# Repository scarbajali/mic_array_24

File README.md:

# mic_array_24
PCB of a 24-MEMS microphones array

**Software:** Kicad

**3D Preview:**

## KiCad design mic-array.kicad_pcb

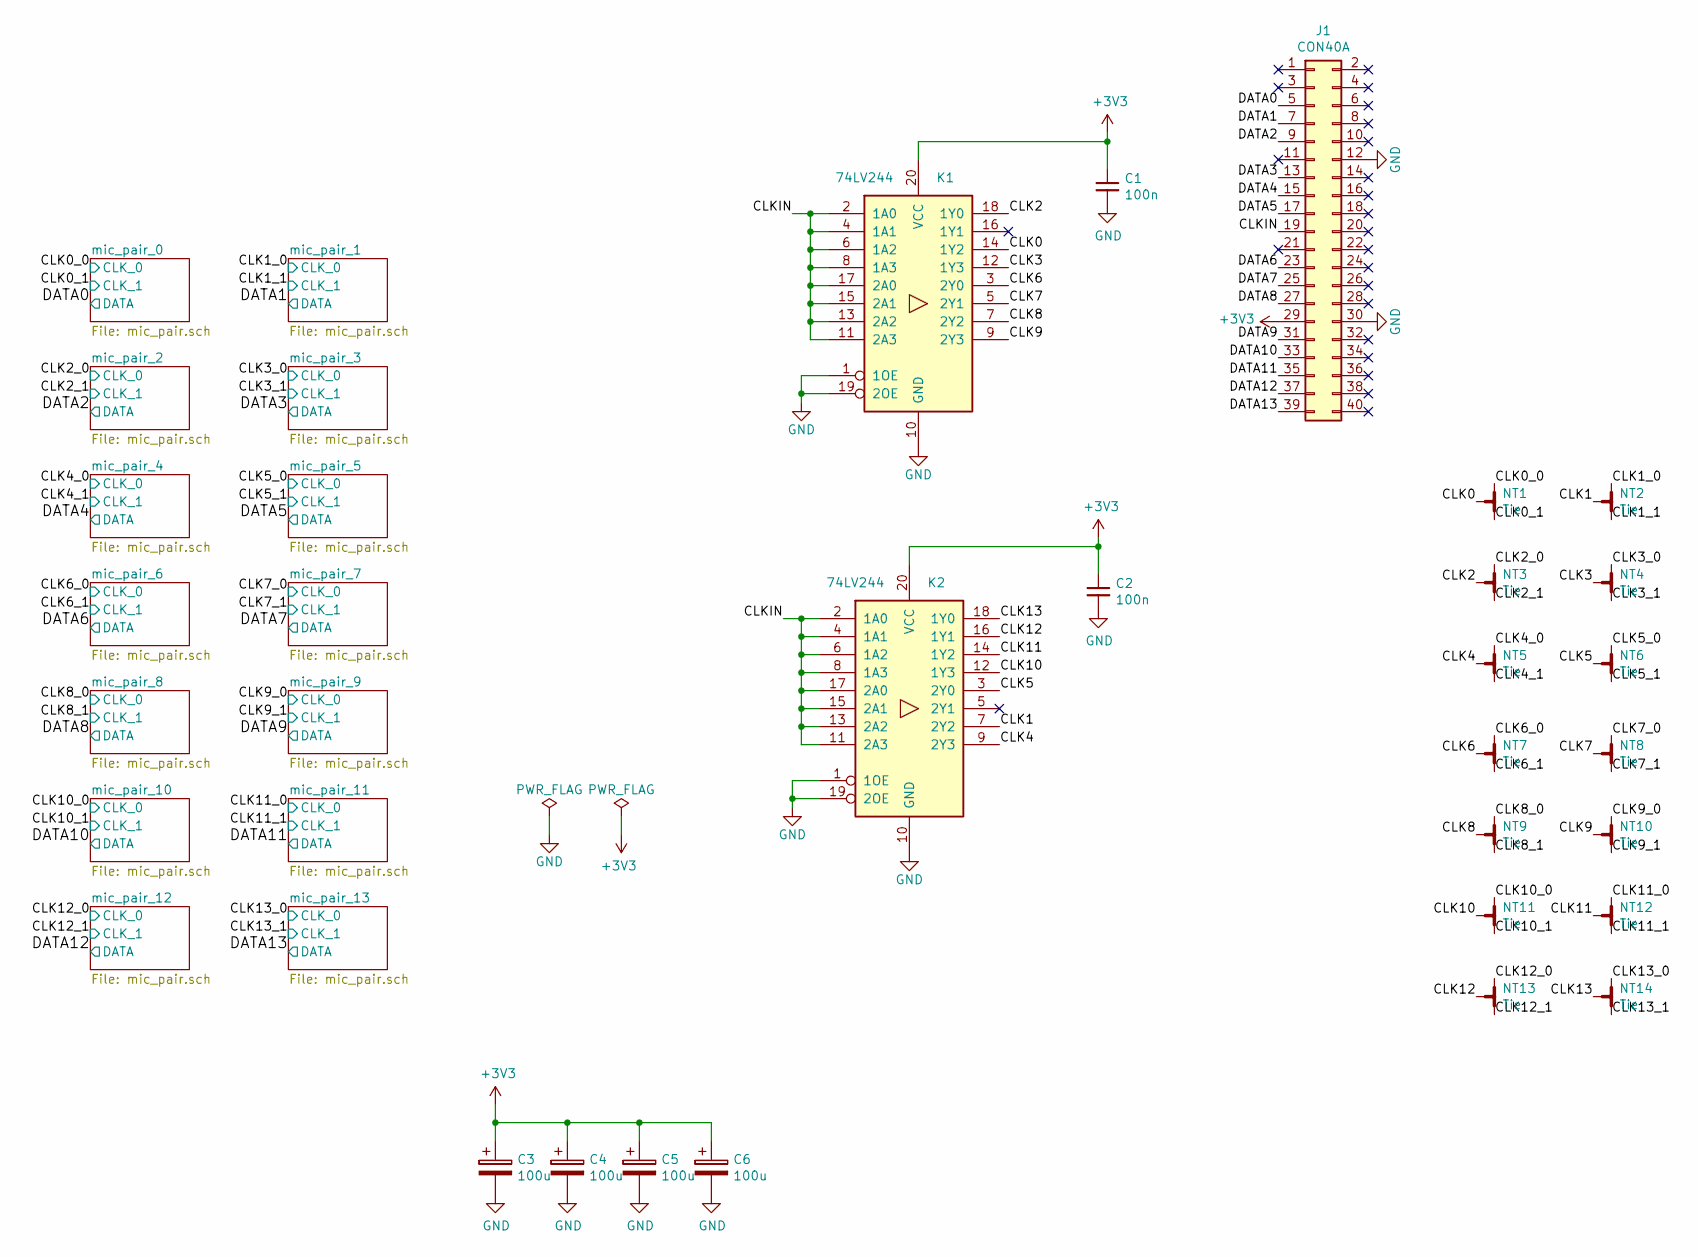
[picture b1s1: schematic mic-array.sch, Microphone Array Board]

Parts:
C1, C2: 100n; C_0603_1608Metric_Pad1.05x0.95mm_HandSolder
C3, C4, C5, C6: 100u; CP_Elec_3x5.3
J1: CON40A; PinSocket_2x20_P2.54mm_Vertical
K1, K2: 74LV244; SSOP-20_4.4x6.5mm_P0.65mm
NT1, NT2, NT3, NT4, NT5, NT6, NT7, NT8, NT9, NT10, NT11, NT12, NT13, NT14: Tie; bridge_1x2_0.12mm

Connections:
+3V3: C1.1, C2.1, C3.1, C4.1, C5.1, C6.1, J1.29, K1.20 (VCC), K2.20 (VCC); also elsewhere on the board
/CLK0: K1.14 (1Y2), NT1.3
/CLK0_0: NT1.1; also elsewhere on the board
/CLK0_1: NT1.2; also elsewhere on the board
/CLK1: K2.7 (2Y2), NT2.3
/CLK1_0: NT2.1; also elsewhere on the board
/CLK1_1: NT2.2; also elsewhere on the board
/CLK2: K1.18 (1Y0), NT3.3
/CLK2_0: NT3.1; also elsewhere on the board
/CLK2_1: NT3.2; also elsewhere on the board
/CLK3: K1.12 (1Y3), NT4.3
/CLK3_0: NT4.1; also elsewhere on the board
/CLK3_1: NT4.2; also elsewhere on the board
/CLK4: K2.9 (2Y3), NT5.3
/CLK4_0: NT5.1; also elsewhere on the board
/CLK4_1: NT5.2; also elsewhere on the board
/CLK5: K2.3 (2Y0), NT6.3
/CLK5_0: NT6.1; also elsewhere on the board
/CLK5_1: NT6.2; also elsewhere on the board
/CLK6: K1.3 (2Y0), NT7.3
/CLK6_0: NT7.1; also elsewhere on the board
/CLK6_1: NT7.2; also elsewhere on the board
/CLK7: K1.5 (2Y1), NT8.3
/CLK7_0: NT8.1; also elsewhere on the board
/CLK7_1: NT8.2; also elsewhere on the board
/CLK8: K1.7 (2Y2), NT9.3
/CLK8_0: NT9.1; also elsewhere on the board
/CLK8_1: NT9.2; also elsewhere on the board
/CLK9: K1.9 (2Y3), NT10.3
/CLK9_0: NT10.1; also elsewhere on the board
/CLK9_1: NT10.2; also elsewhere on the board
/CLK10: K2.12 (1Y3), NT11.3
/CLK10_0: NT11.1; also elsewhere on the board
/CLK10_1: NT11.2; also elsewhere on the board
/CLK11: K2.14 (1Y2), NT12.3
/CLK11_0: NT12.1; also elsewhere on the board
/CLK11_1: NT12.2; also elsewhere on the board
/CLK12: K2.16 (1Y1), NT13.3
/CLK12_0: NT13.1; also elsewhere on the board
/CLK12_1: NT13.2; also elsewhere on the board
/CLK13: K2.18 (1Y0), NT14.3
/CLK13_0: NT14.1; also elsewhere on the board
/CLK13_1: NT14.2; also elsewhere on the board
/CLKIN: J1.19, K1.2 (1A0), K1.4 (1A1), K1.6 (1A2), K1.8 (1A3), K1.11 (2A3), K1.13 (2A2), K1.15 (2A1), K1.17 (2A0), K2.2 (1A0), K2.4 (1A1), K2.6 (1A2), K2.8 (1A3), K2.11 (2A3), K2.13 (2A2), K2.15 (2A1), K2.17 (2A0)
/DATA0: J1.5; also elsewhere on the board
/DATA1: J1.7; also elsewhere on the board
/DATA2: J1.9; also elsewhere on the board
/DATA3: J1.13; also elsewhere on the board
/DATA4: J1.15; also elsewhere on the board
/DATA5: J1.17; also elsewhere on the board
/DATA6: J1.23; also elsewhere on the board
/DATA7: J1.25; also elsewhere on the board
/DATA8: J1.27; also elsewhere on the board
/DATA9: J1.31; also elsewhere on the board
/DATA10: J1.33; also elsewhere on the board
/DATA11: J1.35; also elsewhere on the board
/DATA12: J1.37; also elsewhere on the board
/DATA13: J1.39; also elsewhere on the board
GND: C1.2, C2.2, C3.2, C4.2, C5.2, C6.2, J1.12, J1.30, K1.1 (1OE), K1.10 (GND), K1.19 (2OE), K2.1 (1OE), K2.10 (GND), K2.19 (2OE); also elsewhere on the board

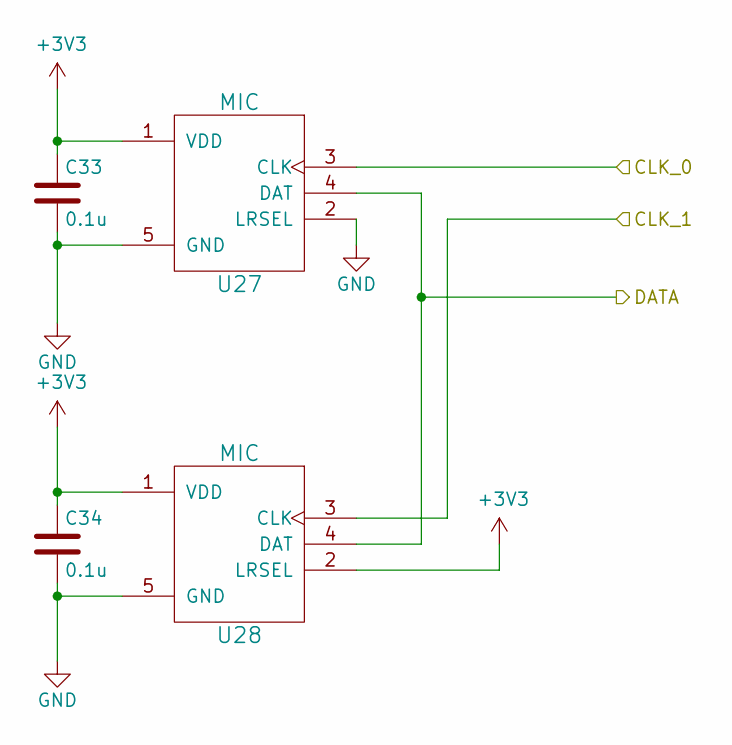
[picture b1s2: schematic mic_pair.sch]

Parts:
C7, C8: 0.1u; C_0603_1608Metric_Pad1.05x0.95mm_HandSolder
U1, U2: MIC; MIC_WM7216

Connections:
+3V3: C7.1, C8.1, U1.1 (VDD), U2.1 (VDD), U2.2 (LRSEL); also elsewhere on the board
/CLK0_0: U1.3 (CLK); also elsewhere on the board
/CLK0_1: U2.3 (CLK); also elsewhere on the board
/DATA0: U1.4 (DAT), U2.4 (DAT); also elsewhere on the board
GND: C7.2, C8.2, U1.2 (LRSEL), U1.5 (GND), U2.5 (GND); also elsewhere on the board

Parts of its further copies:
C9, C10, C11, C12, C13, C14, C15, C16, C17, C18, C19, C20, C21, C22, C23, C24, C25, C26, C27, C28, C29, C30, C31, C32, C33, C34: 0.1u; C_0603_1608Metric_Pad1.05x0.95mm_HandSolder
U3, U4, U5, U6, U7, U8, U9, U10, U11, U12, U13, U14, U15, U16, U17, U18, U19, U20, U21, U22, U23, U24, U25, U26, U27, U28: MIC; MIC_WM7216

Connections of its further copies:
+3V3: C9.1, C10.1, C11.1, C12.1, C13.1, C14.1, C15.1, C16.1, C17.1, C18.1, C19.1, C20.1, C21.1, C22.1, C23.1, C24.1, C25.1, C26.1, C27.1, C28.1, C29.1, C30.1, C31.1, C32.1, C33.1, C34.1, U3.1 (VDD), U4.1 (VDD), U4.2 (LRSEL), U5.1 (VDD), U6.1 (VDD), U6.2 (LRSEL), U7.1 (VDD), U8.1 (VDD), U8.2 (LRSEL), U9.1 (VDD), U10.1 (VDD), U10.2 (LRSEL), U11.1 (VDD), U12.1 (VDD), U12.2 (LRSEL), U13.1 (VDD), U14.1 (VDD), U14.2 (LRSEL), U15.1 (VDD), U16.1 (VDD), U16.2 (LRSEL), U17.1 (VDD), U18.1 (VDD), U18.2 (LRSEL), U19.1 (VDD), U20.1 (VDD), U20.2 (LRSEL), U21.1 (VDD), U22.1 (VDD), U22.2 (LRSEL), U23.1 (VDD), U24.1 (VDD), U24.2 (LRSEL), U25.1 (VDD), U26.1 (VDD), U26.2 (LRSEL), U27.1 (VDD), U28.1 (VDD), U28.2 (LRSEL); also elsewhere on the board
/CLK1_0: U3.3 (CLK); also elsewhere on the board
/CLK1_1: U4.3 (CLK); also elsewhere on the board
/CLK2_0: U5.3 (CLK); also elsewhere on the board
/CLK2_1: U6.3 (CLK); also elsewhere on the board
/CLK3_0: U7.3 (CLK); also elsewhere on the board
/CLK3_1: U8.3 (CLK); also elsewhere on the board
/CLK4_0: U9.3 (CLK); also elsewhere on the board
/CLK4_1: U10.3 (CLK); also elsewhere on the board
/CLK5_0: U11.3 (CLK); also elsewhere on the board
/CLK5_1: U12.3 (CLK); also elsewhere on the board
/CLK6_0: U13.3 (CLK); also elsewhere on the board
/CLK6_1: U14.3 (CLK); also elsewhere on the board
/CLK7_0: U15.3 (CLK); also elsewhere on the board
/CLK7_1: U16.3 (CLK); also elsewhere on the board
/CLK8_0: U17.3 (CLK); also elsewhere on the board
/CLK8_1: U18.3 (CLK); also elsewhere on the board
/CLK9_0: U19.3 (CLK); also elsewhere on the board
/CLK9_1: U20.3 (CLK); also elsewhere on the board
/CLK10_0: U21.3 (CLK); also elsewhere on the board
/CLK10_1: U22.3 (CLK); also elsewhere on the board
/CLK11_0: U23.3 (CLK); also elsewhere on the board
/CLK11_1: U24.3 (CLK); also elsewhere on the board
/CLK12_0: U25.3 (CLK); also elsewhere on the board
/CLK12_1: U26.3 (CLK); also elsewhere on the board
/CLK13_0: U27.3 (CLK); also elsewhere on the board
/CLK13_1: U28.3 (CLK); also elsewhere on the board
/DATA1: U3.4 (DAT), U4.4 (DAT); also elsewhere on the board
/DATA2: U5.4 (DAT), U6.4 (DAT); also elsewhere on the board
/DATA3: U7.4 (DAT), U8.4 (DAT); also elsewhere on the board
/DATA4: U9.4 (DAT), U10.4 (DAT); also elsewhere on the board
/DATA5: U11.4 (DAT), U12.4 (DAT); also elsewhere on the board
/DATA6: U13.4 (DAT), U14.4 (DAT); also elsewhere on the board
/DATA7: U15.4 (DAT), U16.4 (DAT); also elsewhere on the board
/DATA8: U17.4 (DAT), U18.4 (DAT); also elsewhere on the board
/DATA9: U19.4 (DAT), U20.4 (DAT); also elsewhere on the board
/DATA10: U21.4 (DAT), U22.4 (DAT); also elsewhere on the board
/DATA11: U23.4 (DAT), U24.4 (DAT); also elsewhere on the board
/DATA12: U25.4 (DAT), U26.4 (DAT); also elsewhere on the board
/DATA13: U27.4 (DAT), U28.4 (DAT); also elsewhere on the board
GND: C9.2, C10.2, C11.2, C12.2, C13.2, C14.2, C15.2, C16.2, C17.2, C18.2, C19.2, C20.2, C21.2, C22.2, C23.2, C24.2, C25.2, C26.2, C27.2, C28.2, C29.2, C30.2, C31.2, C32.2, C33.2, C34.2, U3.2 (LRSEL), U3.5 (GND), U4.5 (GND), U5.2 (LRSEL), U5.5 (GND), U6.5 (GND), U7.2 (LRSEL), U7.5 (GND), U8.5 (GND), U9.2 (LRSEL), U9.5 (GND), U10.5 (GND), U11.2 (LRSEL), U11.5 (GND), U12.5 (GND), U13.2 (LRSEL), U13.5 (GND), U14.5 (GND), U15.2 (LRSEL), U15.5 (GND), U16.5 (GND), U17.2 (LRSEL), U17.5 (GND), U18.5 (GND), U19.2 (LRSEL), U19.5 (GND), U20.5 (GND), U21.2 (LRSEL), U21.5 (GND), U22.5 (GND), U23.2 (LRSEL), U23.5 (GND), U24.5 (GND), U25.2 (LRSEL), U25.5 (GND), U26.5 (GND), U27.2 (LRSEL), U27.5 (GND), U28.5 (GND); also elsewhere on the board

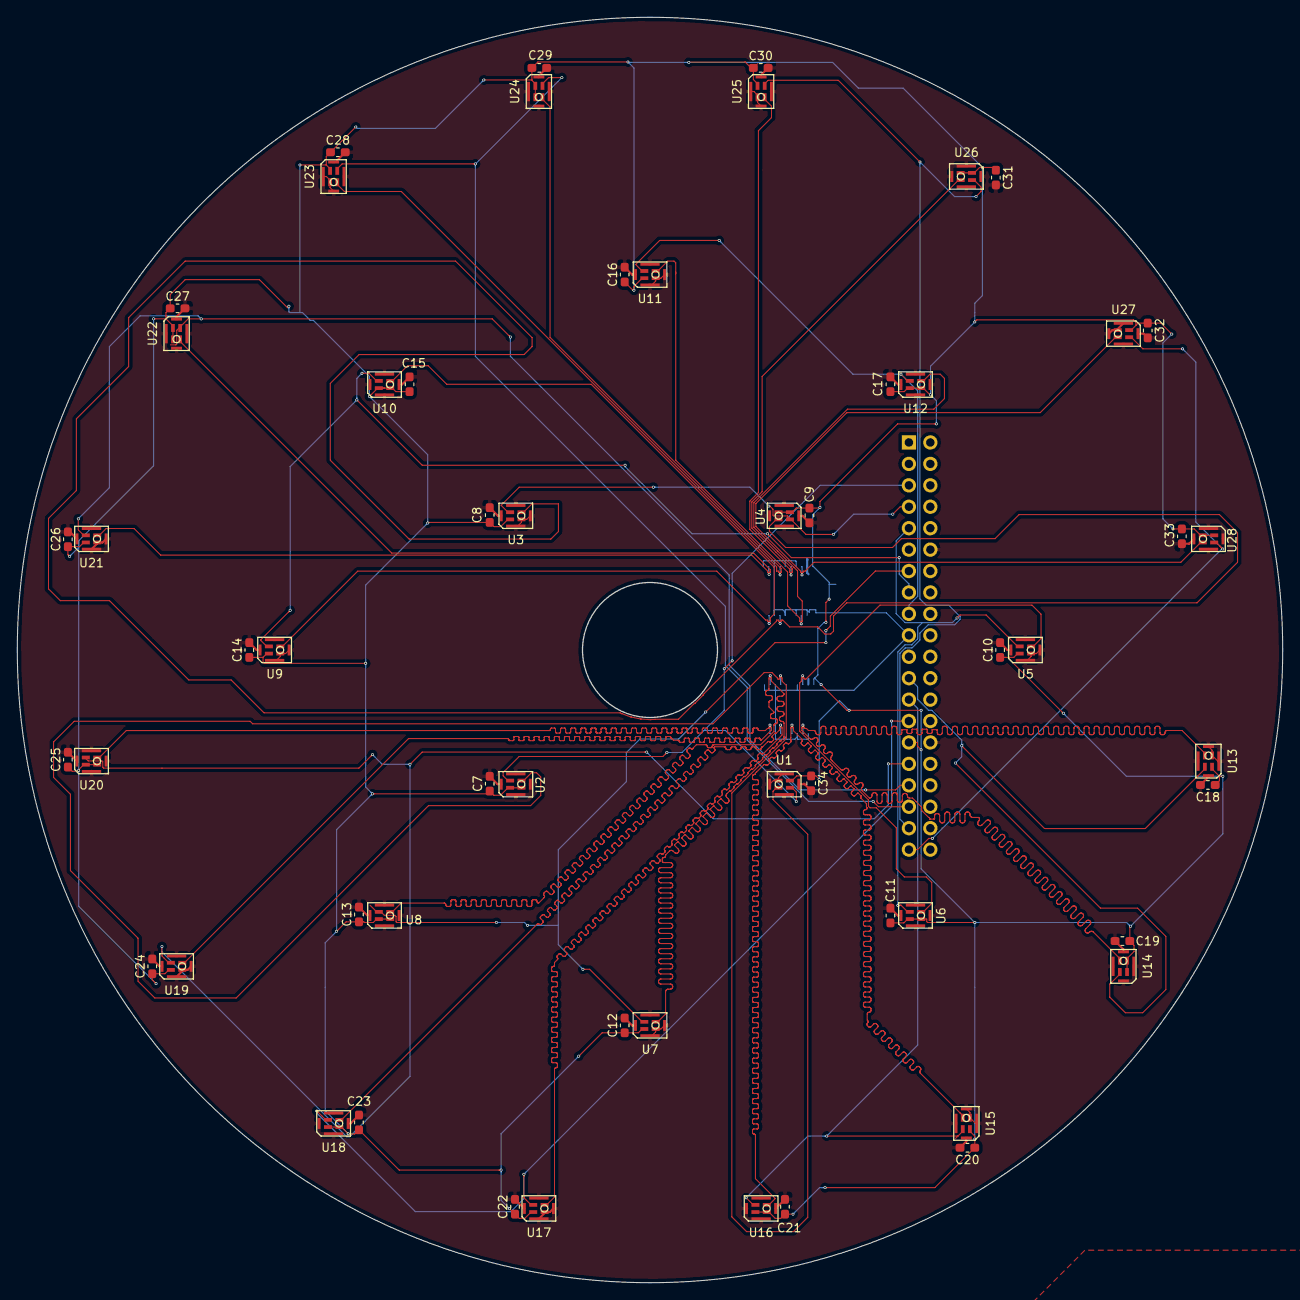
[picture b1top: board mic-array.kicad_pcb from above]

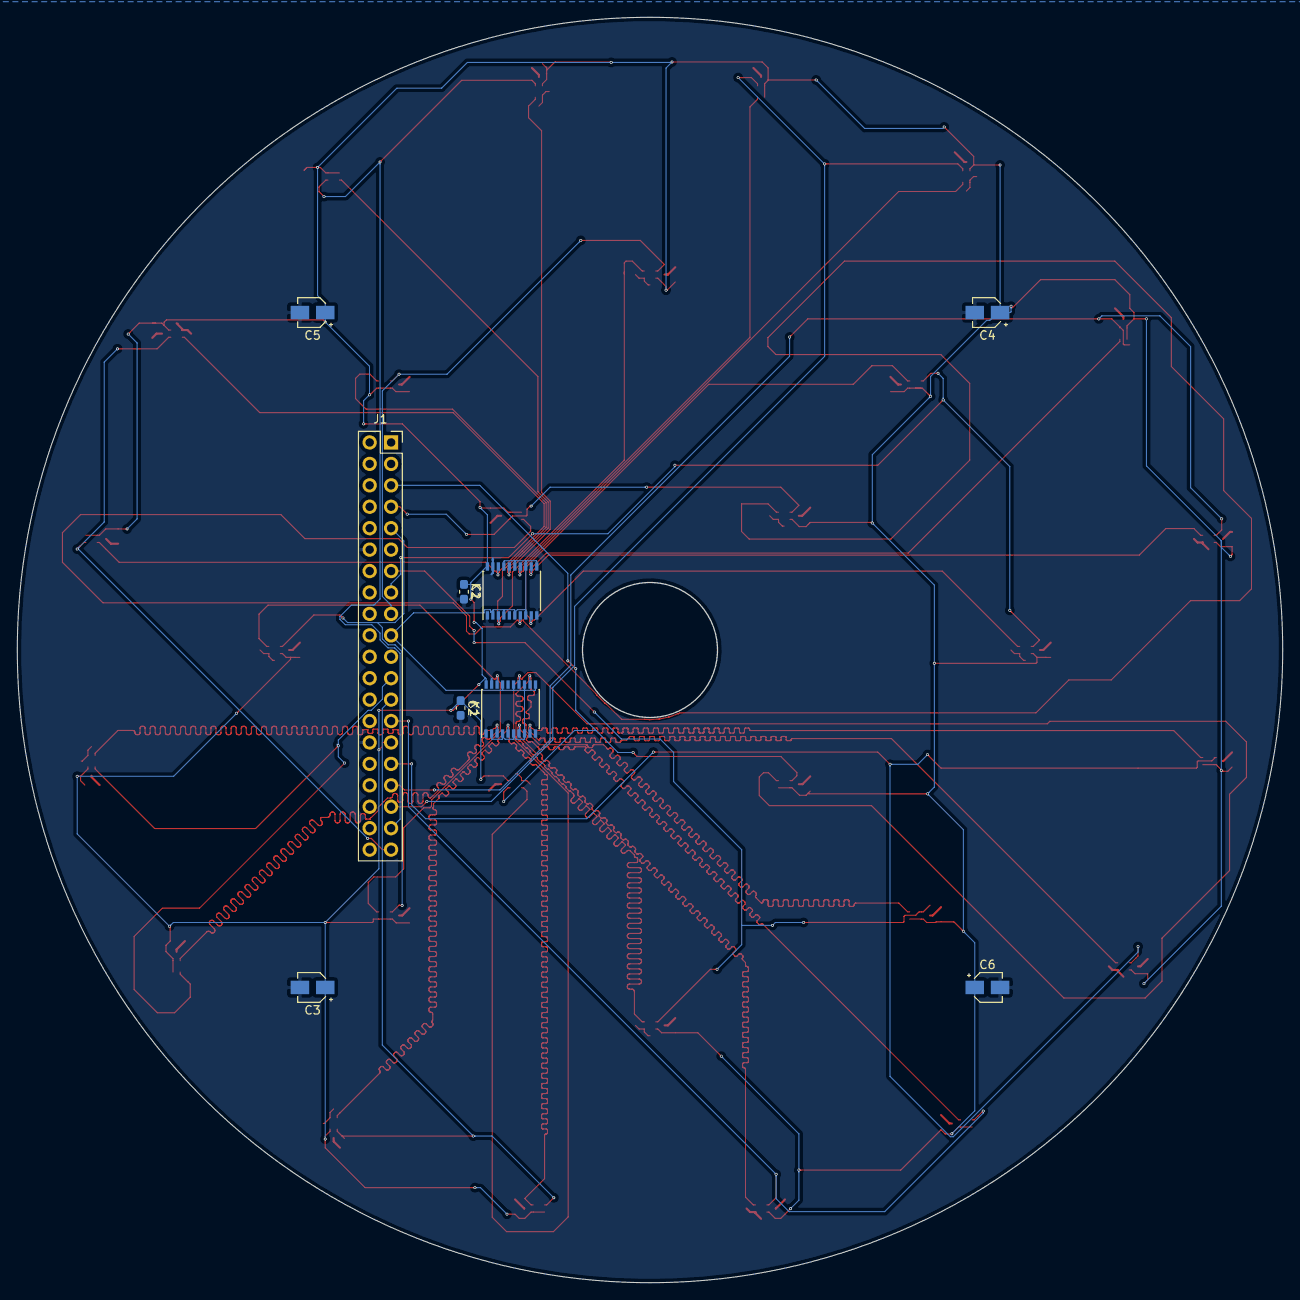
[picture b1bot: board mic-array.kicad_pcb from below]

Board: 2 copper layers, 150.0 x 150.0 mm, 79 parts (9 on the bottom side), 59 nets.

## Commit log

2018-12-11 Initial draft version.
2018-12-13 Add new PCB design with improved constraints and routing. Change connector type to 2.54mm one.
2018-12-14 Add a new buffer to compensate nets impedance.
2018-12-18 Update routing. Resolve all DRC errors and warnings.
2018-12-18 Cosmetic only.
2021-07-11 Create LICENSE
2021-07-11 Add 3D preview image.
